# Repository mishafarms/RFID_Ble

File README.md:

# RFID_Ble
BLE RFID reader

Here is a link to the PCB for this design. https://oshpark.com/shared_projects/lGCXMxED

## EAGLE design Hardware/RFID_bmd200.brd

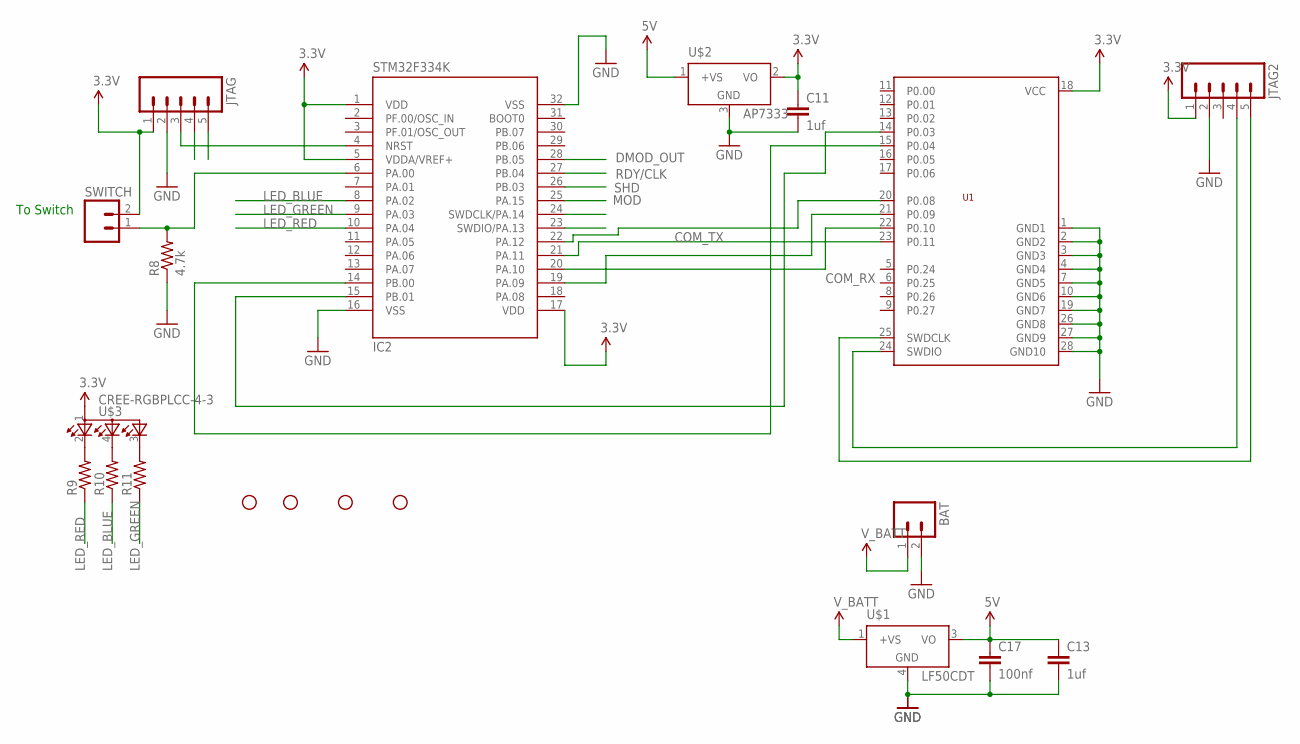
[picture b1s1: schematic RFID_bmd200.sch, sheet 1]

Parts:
BAT: M02PTH; 1X02
C11, C13: 1uf; 0805
C17: 100nf; 0805
IC2: STM32F334K; LQFP-32
JTAG, JTAG2: M05PTH; 1X05
R8: 4.7k; 0805
R9, R10, R11: RESISTOR0805-RES; 0805
STANDOFF1, STANDOFF2, STANDOFF3, STANDOFF4: STAND-OFF
SWITCH: M02PTH; 1X02
U1: BMD-200
U$1: LF50CDT; DPACK_3
U$2: AP7333; SOT23-3
U$3: CREE-RGBPLCC-4-3; P-LCC-4-3

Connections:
3.3V: C11.1, IC2.1 (VDD), IC2.5 (VDDA/VREF+), IC2.17 (VDD), JTAG.1, JTAG2.1, SWITCH.2, U1.18 (VCC), U$2.2 (VO), U$3.1 (A2)
5V: C13.1, C17.1, U$1.3 (VO), U$2.1 (+VS); also elsewhere on the board
COM_RX: IC2.20 (PA.10), U1.22 (P0.10)
COM_TX: IC2.19 (PA.09), U1.21 (P0.09)
DMOD_OUT: IC2.28 (PB.05); also elsewhere on the board
GND: BAT.2, C11.2, C13.2, C17.2, IC2.16 (VSS), IC2.32 (VSS), JTAG.2, JTAG2.2, R8.1, U1.1 (GND1), U1.2 (GND2), U1.3 (GND3), U1.4 (GND4), U1.7 (GND5), U1.10 (GND6), U1.19 (GND7), U1.26 (GND8), U1.27 (GND9), U1.28 (GND10), U$1.4 (GND), U$2.3 (GND); also elsewhere on the board
LED_BLUE: IC2.8 (PA.02), R10.1
LED_GREEN: IC2.9 (PA.03), R11.1
LED_RED: IC2.10 (PA.04), R9.1
MOD: IC2.25 (PA.15); also elsewhere on the board
unnamed: IC2.6 (PA.00), R8.2, SWITCH.1
unnamed: IC2.22 (PA.12), U1.20 (P0.08)
unnamed: IC2.21 (PA.11), U1.23 (P0.11)
unnamed: IC2.15 (PB.01), U1.14 (P0.03)
unnamed: JTAG2.5, U1.25 (SWDCLK)
unnamed: JTAG2.4, U1.24 (SWDIO)
unnamed: IC2.14 (PB.00), U1.15 (P0.04)
unnamed: R9.2, U$3.2 (CRED)
unnamed: R10.2, U$3.4 (CBLUE)
unnamed: IC2.4 (NRST), JTAG.3
unnamed: R11.2, U$3.3 (CGREEN)
RDY/CLK: IC2.27 (PB.04); also elsewhere on the board
SHD: IC2.26 (PB.03); also elsewhere on the board
STM_SWDCLK: IC2.24 (SWDCLK/PA.14), JTAG.5
STM_SWDIO: IC2.23 (SWDIO/PA.13), JTAG.4
V_BATT: BAT.1, U$1.1 (+VS)

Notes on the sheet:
To Switch

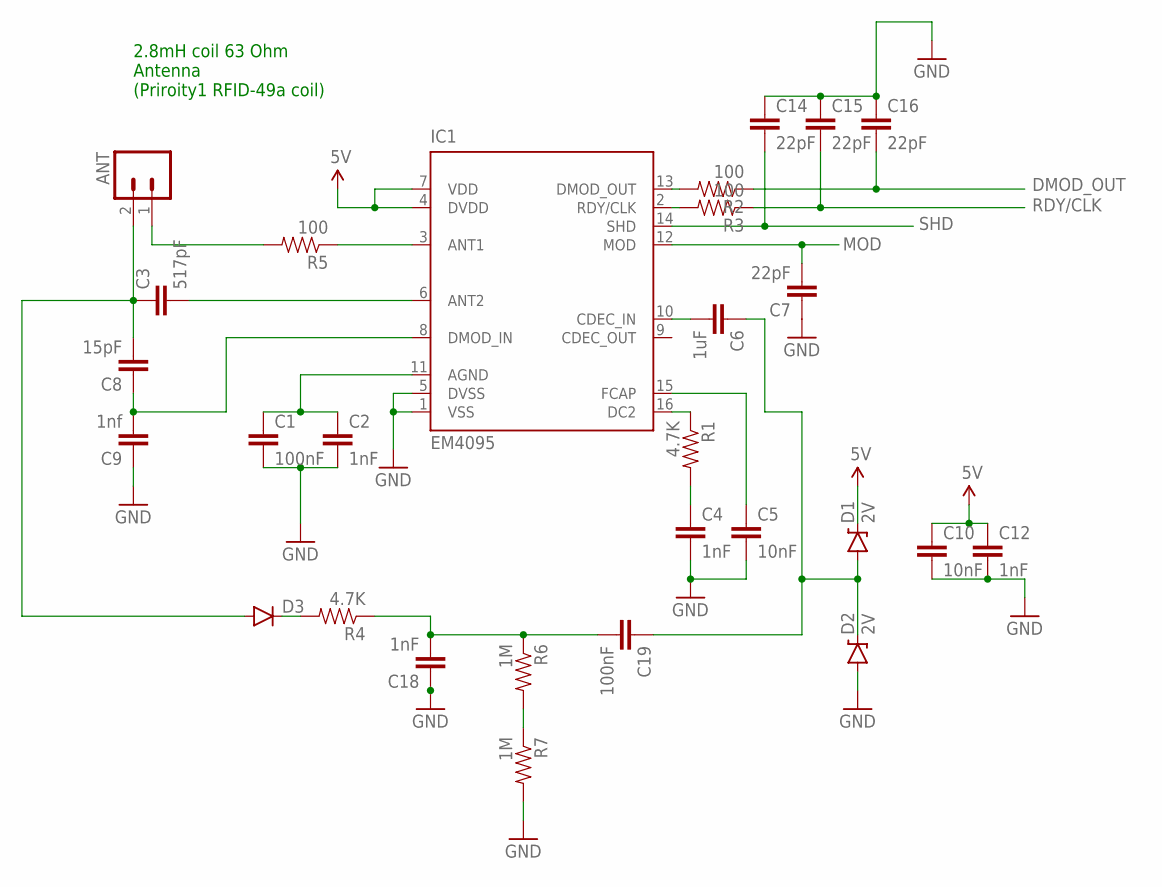
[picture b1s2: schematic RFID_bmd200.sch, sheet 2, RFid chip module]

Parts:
ANT: M02PTH; 1X02
C1: 100nF; 0805
C2, C4, C12, C18: 1nF; 0805
C3: 517pF; 0805
C5, C10: 10nF; 0805
C6: 1uF; 0805
C7, C14, C15, C16: 22pF; 0805
C8: 15pF; 0805
C9: 1nf; 0805
C19: 100nF; C1812
D1, D2: 2V; SOD-123
D3: DIODESMF; SMF
IC1: EM4095; SO16
R1, R4: 4.7K; 0805
R2, R3, R5: 100; 0805
R6, R7: 1M; 0805

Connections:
5V: C10.1, C12.1, D1.C, IC1.4 (DVDD), IC1.7 (VDD); also elsewhere on the board
ANT1: ANT.1, R5.2
DMOD_OUT: C16.2, R2.1; also elsewhere on the board
GND: C1.2, C2.2, C4.2, C5.2, C7.1, C9.1, C10.2, C12.2, C14.1, C15.1, C16.1, C18.1, D2.A, IC1.1 (VSS), IC1.5 (DVSS), R7.2; also elsewhere on the board
MOD: C7.2, IC1.12 (MOD); also elsewhere on the board
unnamed: IC1.13 (DMOD_OUT), R2.2
unnamed: IC1.2 (RDY/CLK), R3.2
unnamed: C6.2, IC1.10 (CDEC_IN)
unnamed: R6.2, R7.1
unnamed: C5.1, IC1.15 (FCAP)
unnamed: C4.1, R1.2
unnamed: IC1.16 (DC2), R1.1
unnamed: IC1.3 (ANT1), R5.1
unnamed: C3.2, IC1.6 (ANT2)
unnamed: ANT.2, C3.1, C8.2, D3.P$2 (A)
unnamed: C1.1, C2.1, IC1.11 (AGND)
unnamed: C8.1, C9.2, IC1.8 (DMOD_IN)
unnamed: C18.2, C19.2, R4.1, R6.1
unnamed: C6.1, C19.1, D1.A, D2.C
unnamed: D3.P$1 (C), R4.2
RDY/CLK: C15.2, R3.1; also elsewhere on the board
SHD: C14.2, IC1.14 (SHD); also elsewhere on the board

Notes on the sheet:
2.8mH coil 63 Ohm Antenna (Priroity1 RFID-49a coil)

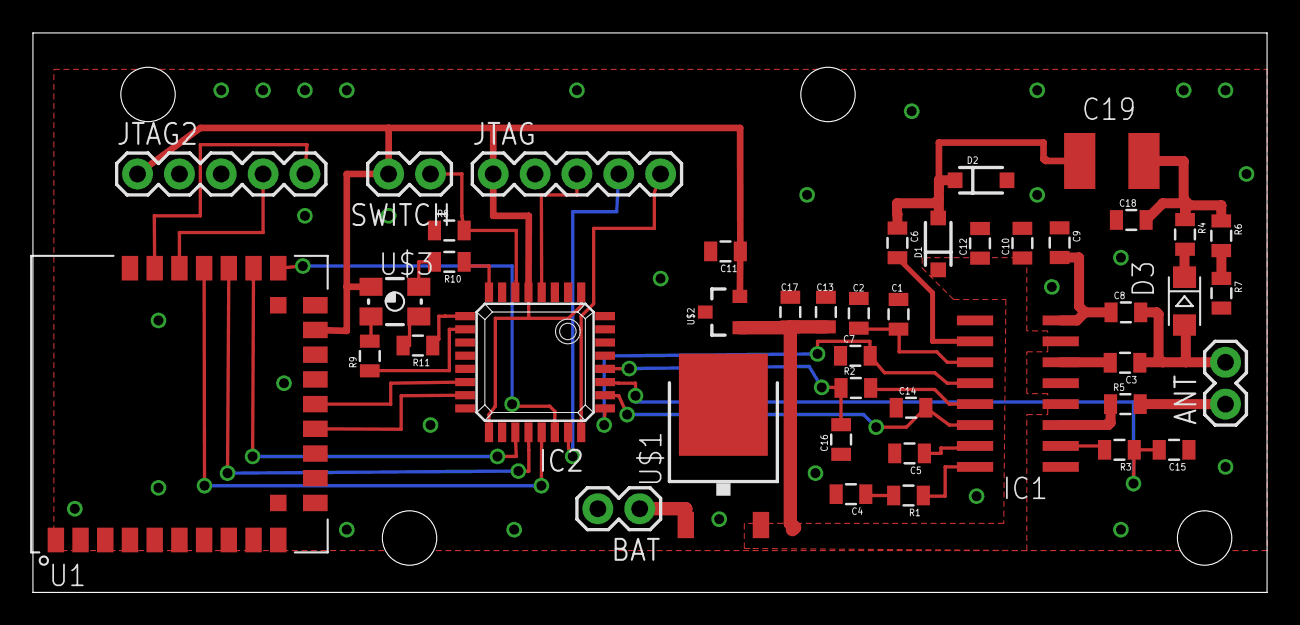
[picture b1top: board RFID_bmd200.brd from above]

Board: 2 copper layers, 74.9 x 34.0 mm, 48 parts (0 on the bottom side), 42 nets.

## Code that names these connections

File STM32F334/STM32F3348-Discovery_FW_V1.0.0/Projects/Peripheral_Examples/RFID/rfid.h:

/**
  ******************************************************************************
  * @file    TIM_PWM_Input/main.h 
  * @author  MCD Application Team
  * @version V1.0.0
  * @date    20-June-2014
  * @brief   Header for main.c module
  ******************************************************************************
  * @attention
  *
  * <h2><center>&copy; COPYRIGHT 2014 STMicroelectronics</center></h2>
  *
  * Licensed under MCD-ST Liberty SW License Agreement V2, (the "License");
  * You may not use this file except in compliance with the License.
  * You may obtain a copy of the License at:
  *
  *        http://www.st.com/software_license_agreement_liberty_v2
  *
  * Unless required by applicable law or agreed to in writing, software 
  * distributed under the License is distributed on an "AS IS" BASIS, 
  * WITHOUT WARRANTIES OR CONDITIONS OF ANY KIND, either express or implied.
  * See the License for the specific language governing permissions and
  * limitations under the License.
  *
  ******************************************************************************
  */
  
/* Define to prevent recursive inclusion -------------------------------------*/
#ifndef __RFID_H
#define __RFID_H

/* Includes ------------------------------------------------------------------*/

#include "main.h"
#include <string.h>
#include "SEGGER_RTT.h"

/* Exported types ------------------------------------------------------------*/
/* Exported constants --------------------------------------------------------*/
/* Exported macro ------------------------------------------------------------*/

#define MAX_UINT8 255
#define CAPTURE_SIZE 88

#define FALSE (0)
#define TRUE (!FALSE)

#define SLEEP_TIMEOUT  (1000 * 60 * 2)   // 2 minutes in milliseconds
//#define SLEEP_TIMEOUT  (1000 * 10)   // 30 seconds in milliseconds

/* There will be more if I decide to support other formats (likely) */

#define DECODE_NUMBER_BIPHASE 2

/* Exported functions ------------------------------------------------------- */

extern void USART1_Configuration(void);
extern void USART1_SendStr(char *str);
extern void USART2_SendStr(char *str);

extern void Timing_Tick(void);
extern void Delay(__IO uint32_t nTime);

/* button.c */

extern void Button_Config(void);
extern void Button_Handler(void);
extern uint8_t Button_State(void);
extern void Sleep_Button_Press(void);

/* led.c */

#define LED_BLACK  0
#define LED_BLUE   1
#define LED_GREEN  2
#define LED_CYAN   3
#define LED_RED    4
#define LED_PURPLE 5
#define LED_YELLOW 6
#define LED_WHITE  7

#define LED_FAST_CYCLE 400
#define LED_SLOW_CYCLE 800

extern void Led_Config(void);
extern void Led_Tick(void);
extern void Led_Set(uint8_t color);
extern void Led_Set_Cycle(uint32_t time);
extern uint8_t Led_Set_Temp(uint8_t color, uint32_t time);
extern uint8_t Led_Off(void);
extern uint8_t Led_On(void);

extern void Ble_Led_Flash(void);

/* timer.c */

extern void (*decode)(uint32_t, uint32_t);      //decoder routine variable

extern void TIM_Config(void);
extern void timerEnableCapture(void);

void timerStopInts(void);
void timerStop(void);

uint32_t timerGetCounter(void);
void timerSetCounter(uint32_t cnt);
void waitForTimer(void);

/* capture.c */

char *AnimalCapture(void);
void Capture(uint8_t style);
uint8_t SearchPattern( uint32_t pattern, uint32_t mask, uint8_t start, uint8_t size );

/* main.c still */

extern void RCC_Configuration(void);

extern uint8_t capture_data[CAPTURE_SIZE];
extern uint8_t capture_valid[CAPTURE_SIZE];
extern __IO uint8_t currentMaxTimeHi;

extern void biPhaseCapture(uint32_t, uint32_t);
extern __IO uint32_t timerDone;
extern uint32_t getTick(void);
extern uint8_t goodStr;

#endif /* __RFID_H */

/************************ (C) COPYRIGHT STMicroelectronics *****END OF FILE****/

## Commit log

2016-02-24 Added files via upload
    Initial board design. Already we need version 0.2
2016-02-24 moved these files to hardware directory
2016-02-24 moved these
2016-02-24 fixed some missing grounds and changed to the RTS pin on the STM32F334
2016-02-24 Initial checkin of the RFID reader code
2016-02-24 moved RFID to the correct project path for the discovery board builds
2016-04-22 just added this
2016-04-22 this all works
2018-03-13 add a link to the PCB
2018-03-13 no really

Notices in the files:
parts and their libraries:
SparkFun-Connectors: Licensing: Creative Commons ShareAlike 4.0 International - https://creativecommons.org/licenses/by-sa/4.0
